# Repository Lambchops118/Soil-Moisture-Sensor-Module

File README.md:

# Soil-Moisture-Sensor-Module
Self contained, solar powered, MQTT communicating module to send soil update to BUTLER

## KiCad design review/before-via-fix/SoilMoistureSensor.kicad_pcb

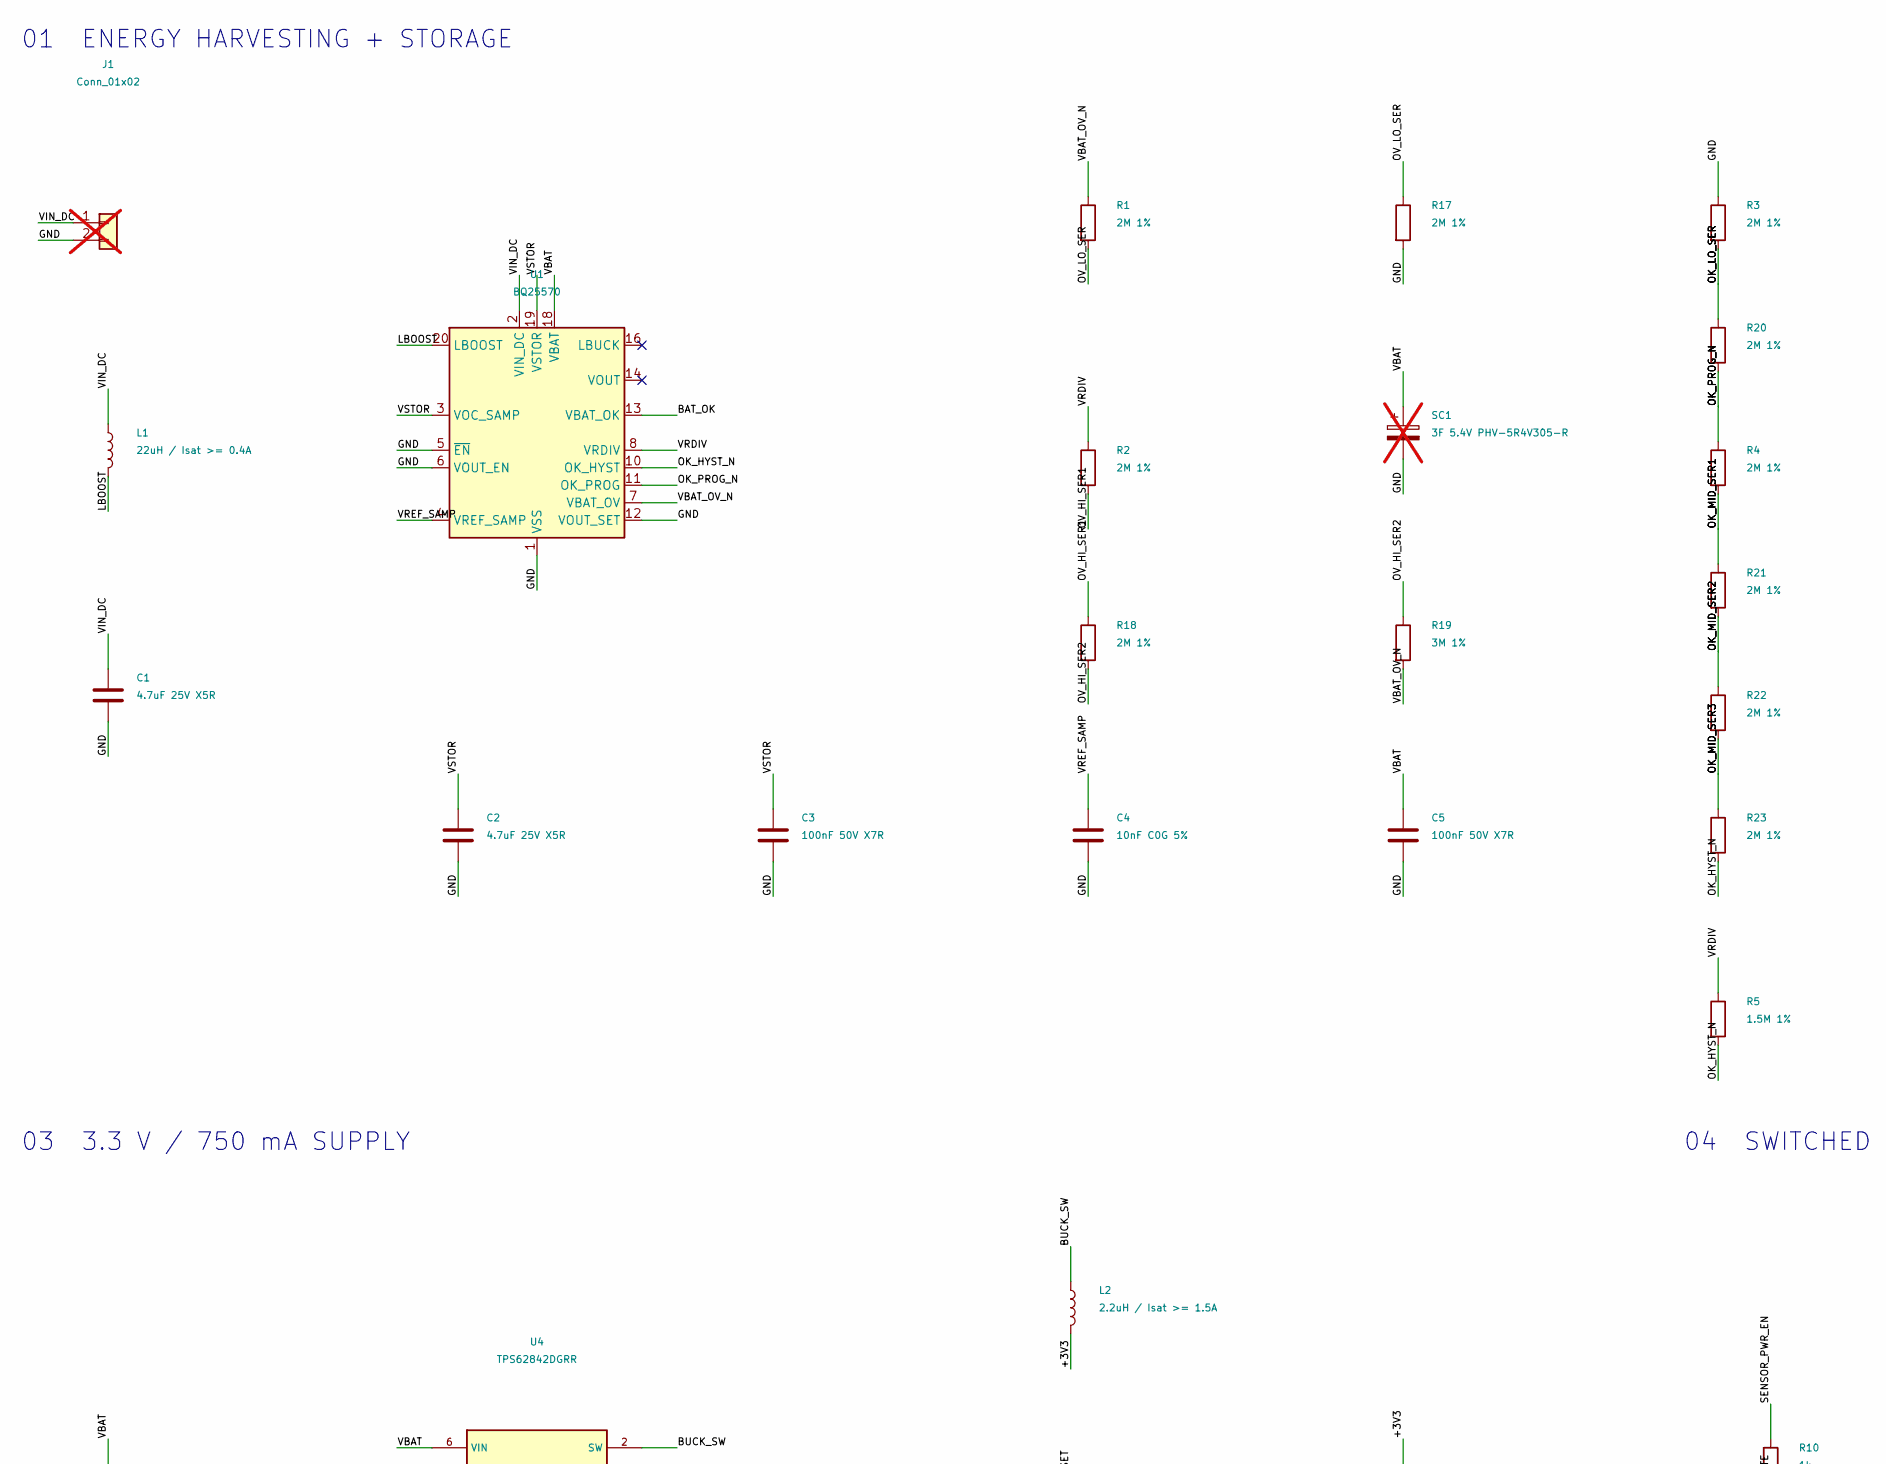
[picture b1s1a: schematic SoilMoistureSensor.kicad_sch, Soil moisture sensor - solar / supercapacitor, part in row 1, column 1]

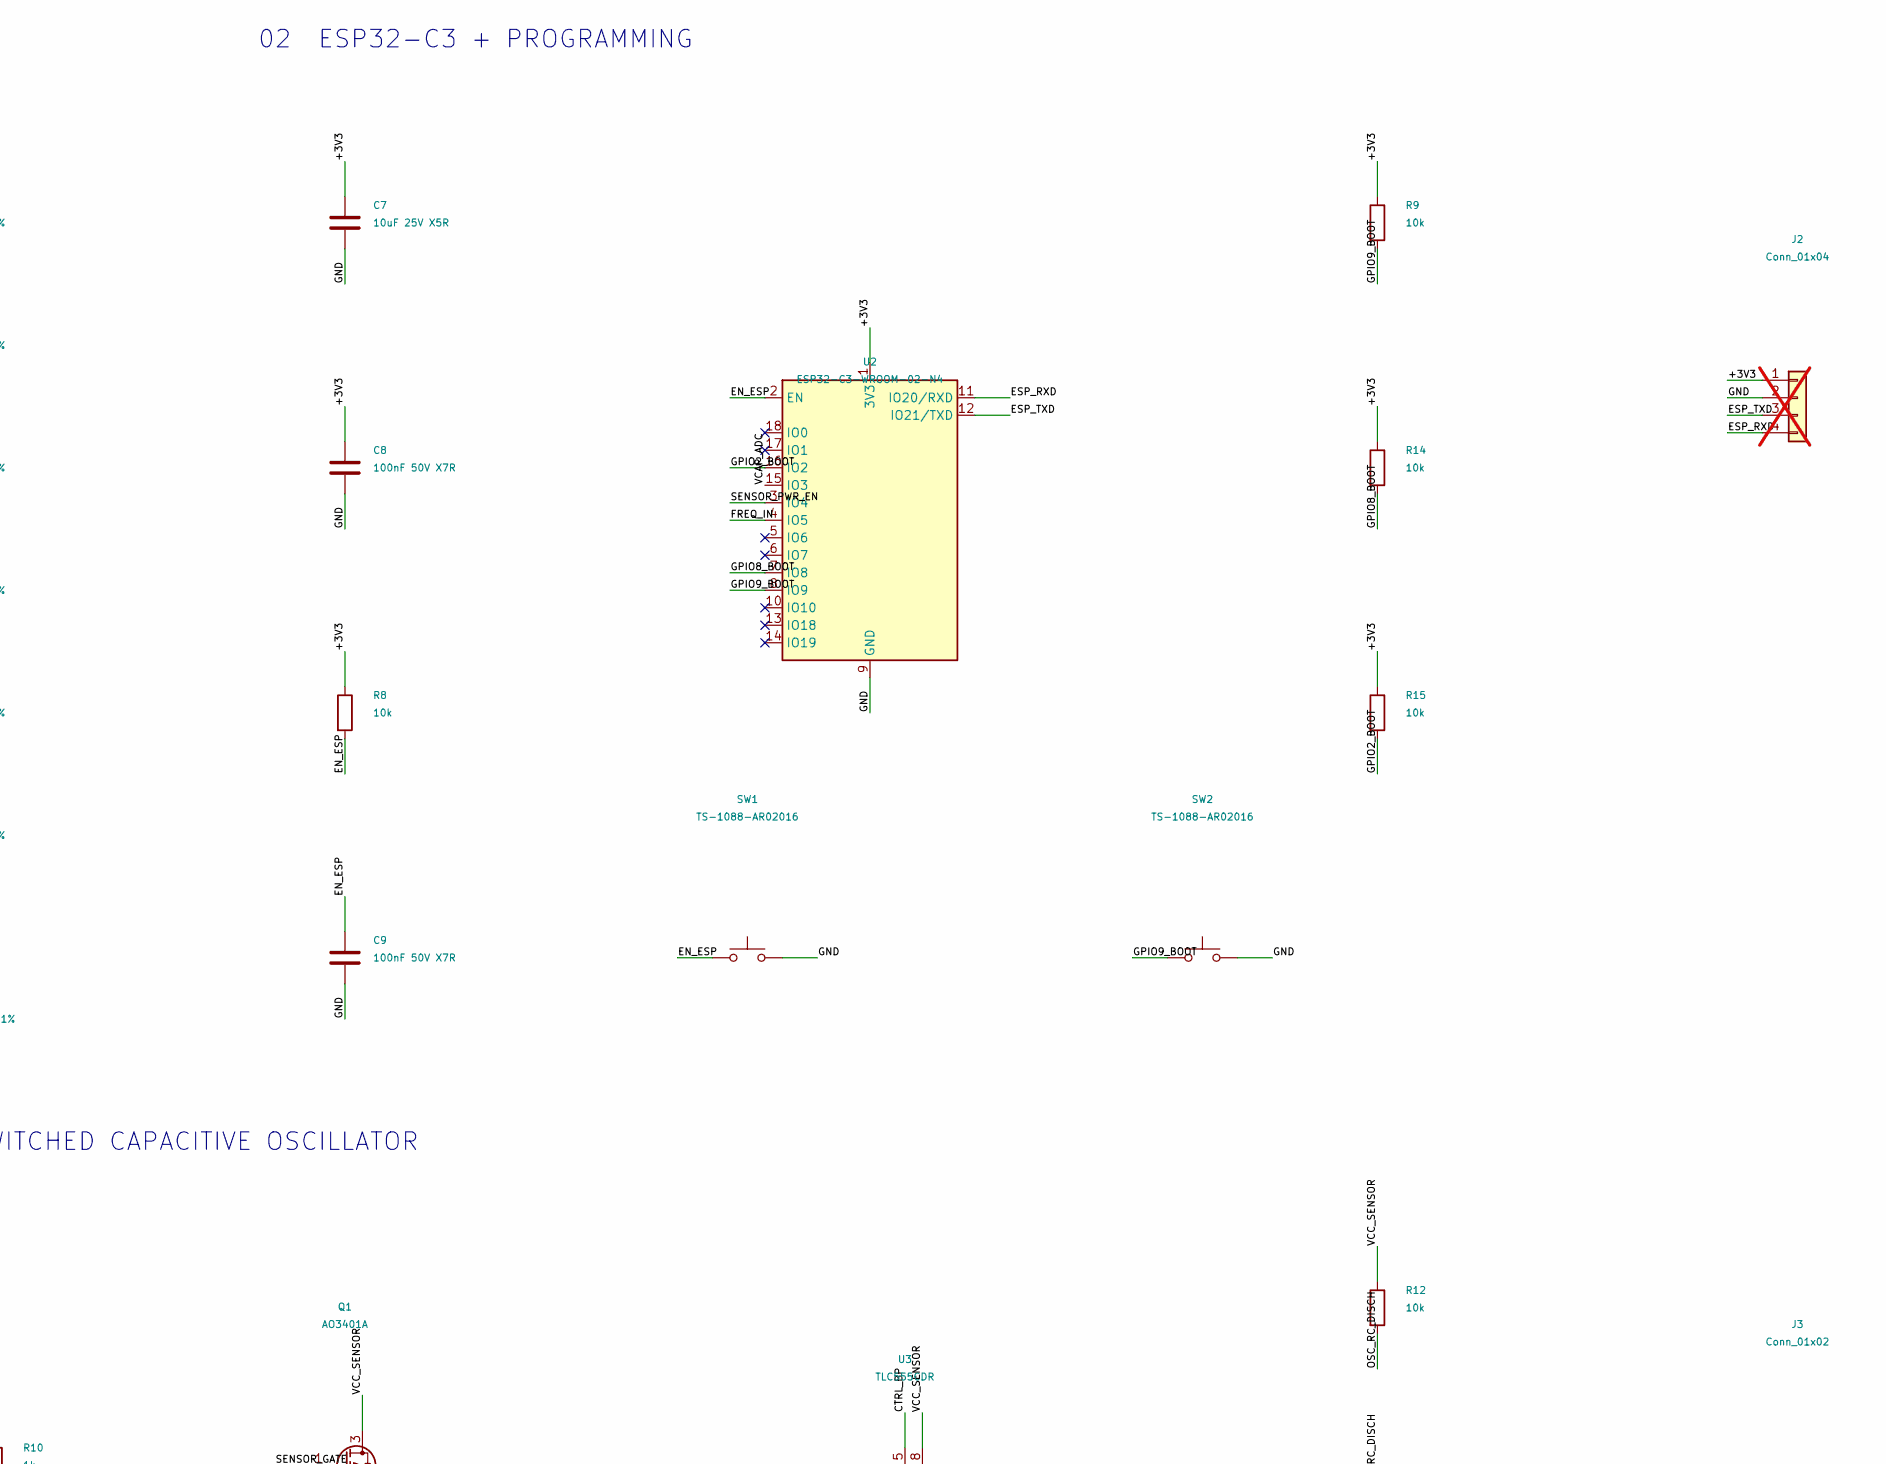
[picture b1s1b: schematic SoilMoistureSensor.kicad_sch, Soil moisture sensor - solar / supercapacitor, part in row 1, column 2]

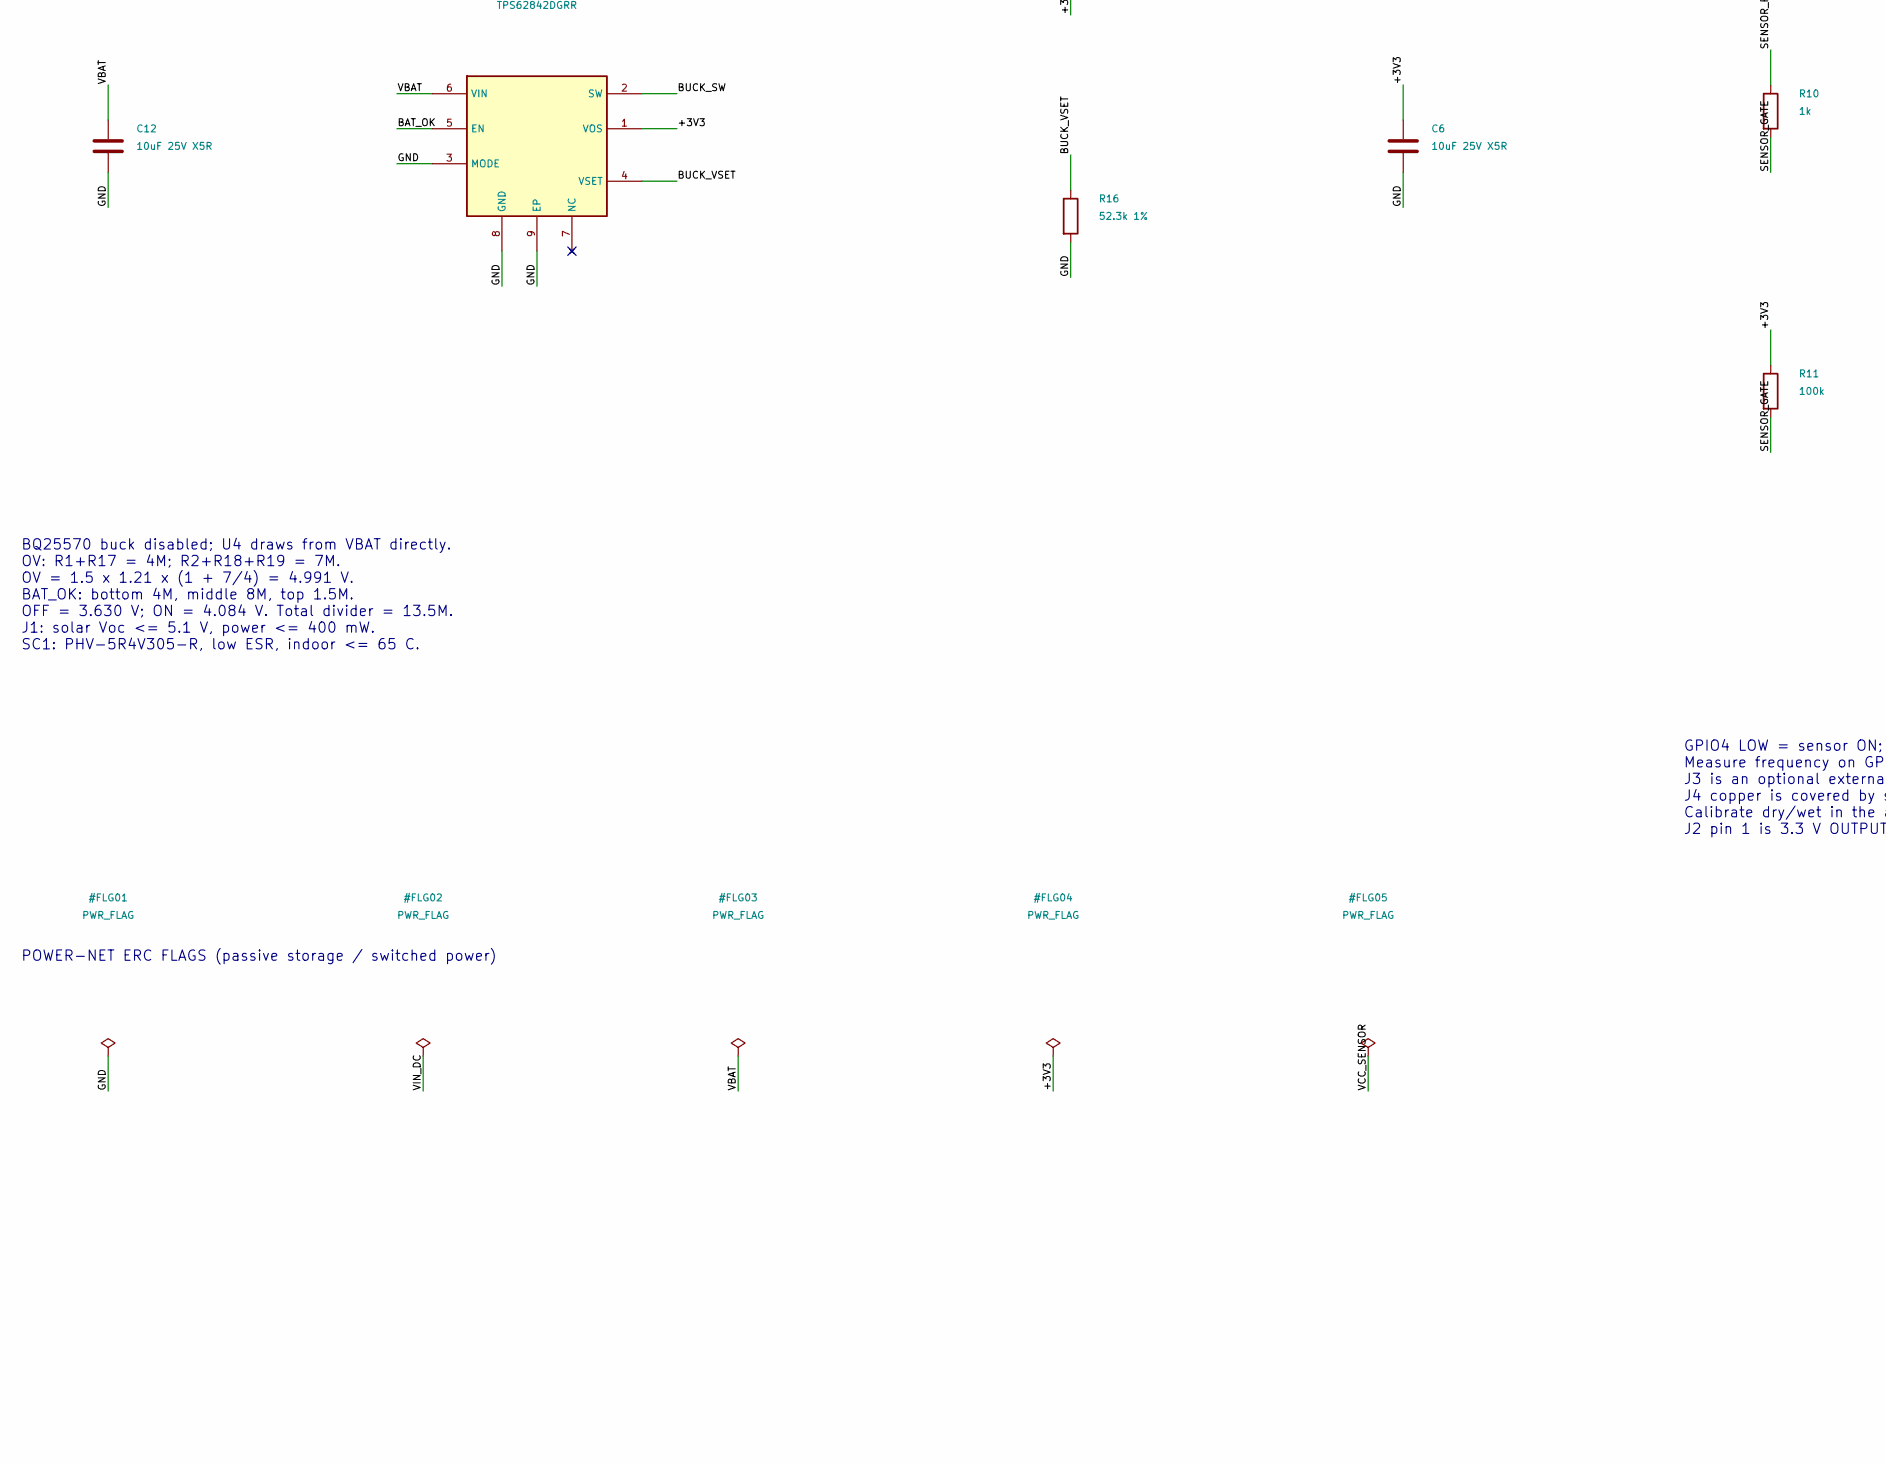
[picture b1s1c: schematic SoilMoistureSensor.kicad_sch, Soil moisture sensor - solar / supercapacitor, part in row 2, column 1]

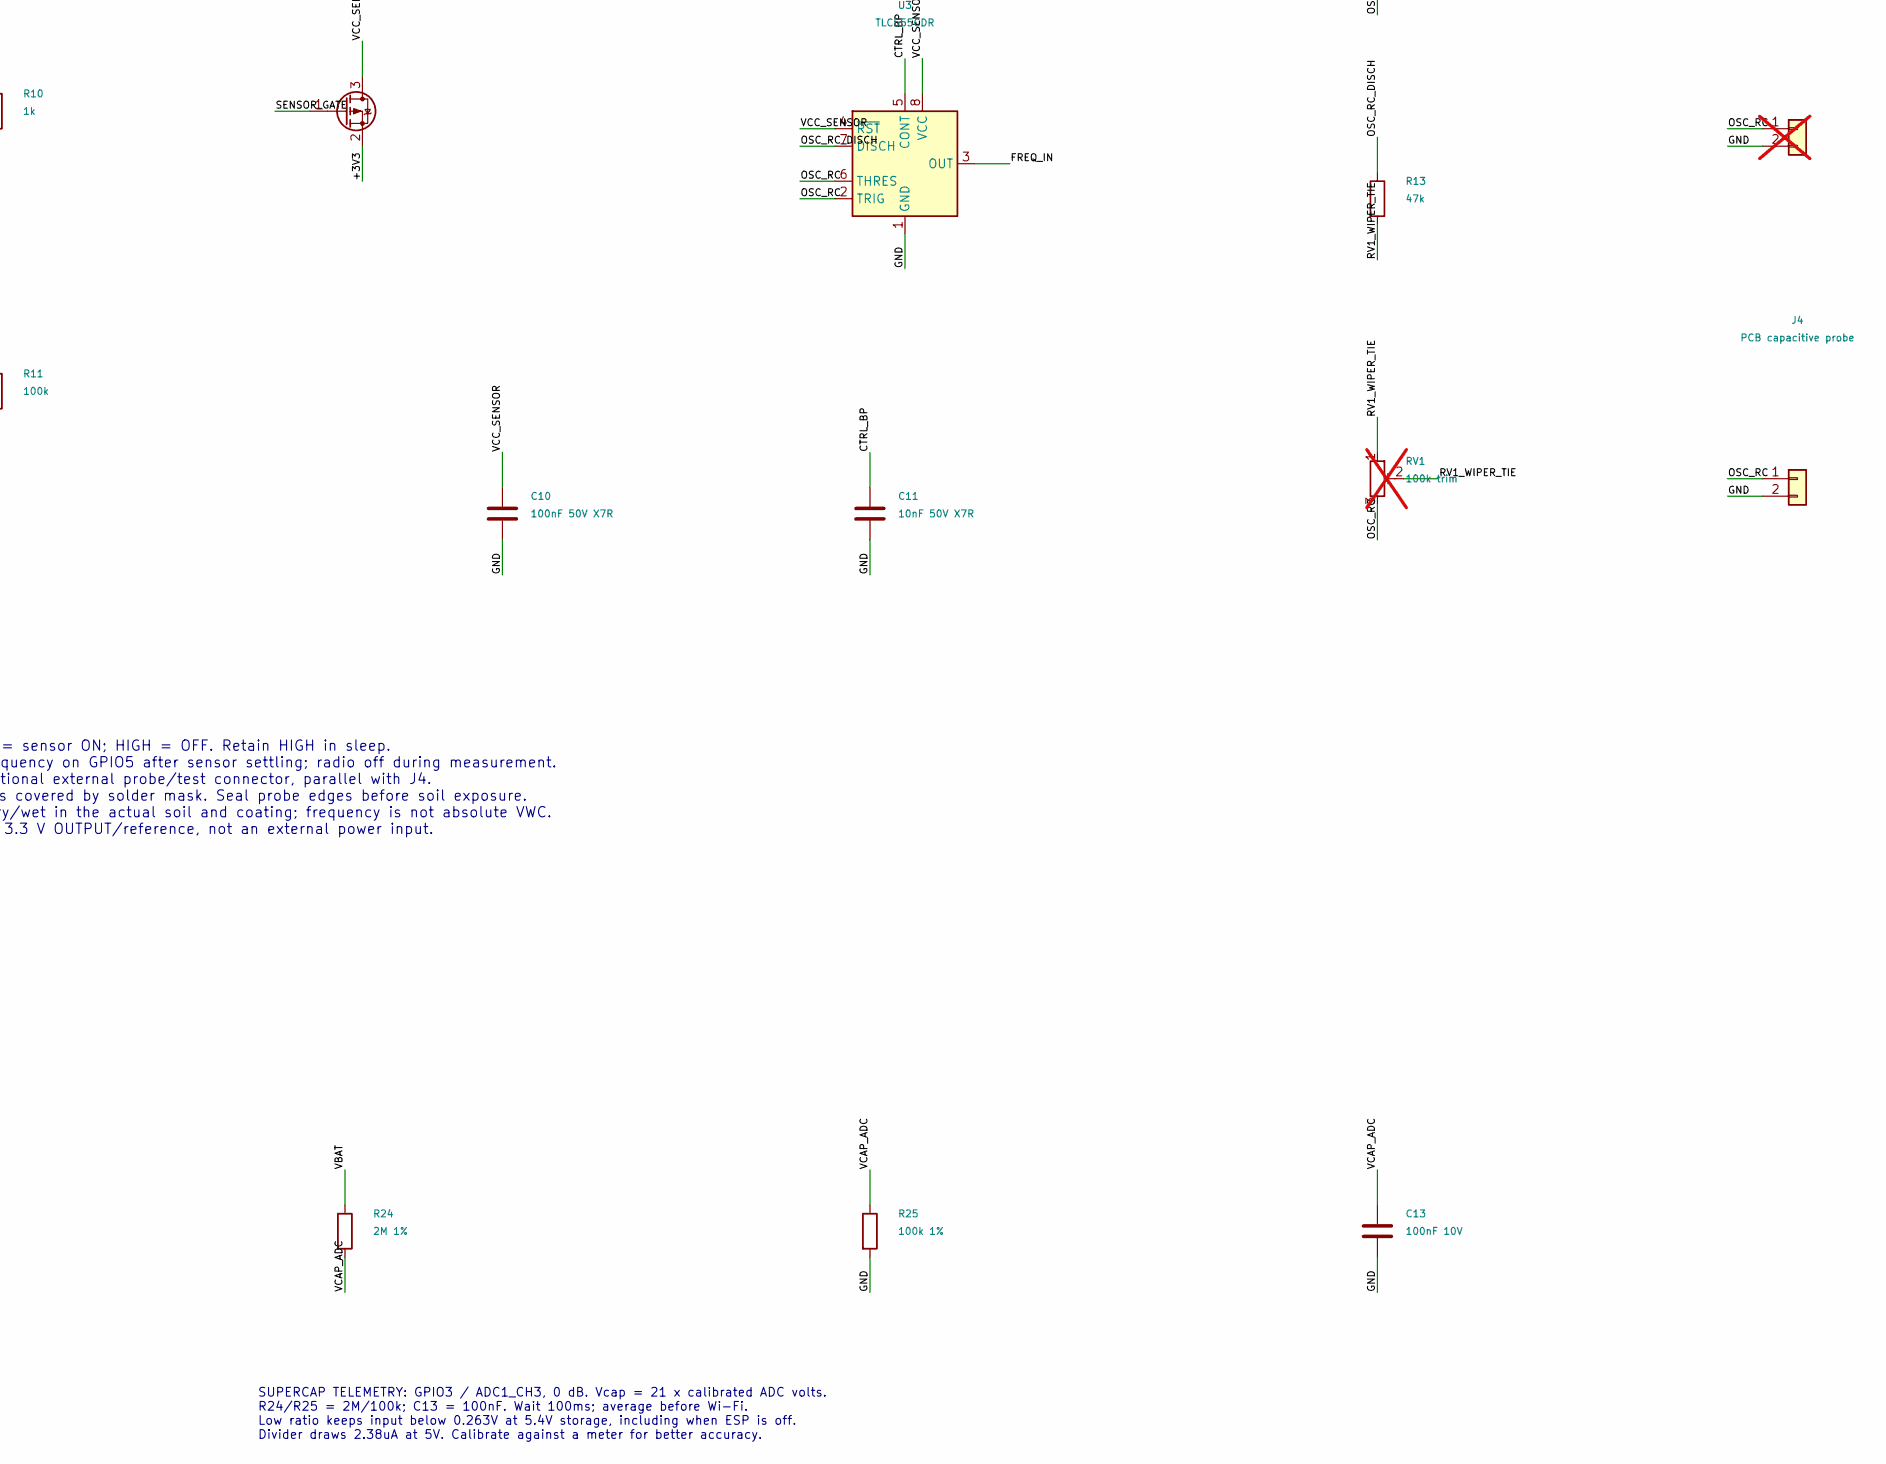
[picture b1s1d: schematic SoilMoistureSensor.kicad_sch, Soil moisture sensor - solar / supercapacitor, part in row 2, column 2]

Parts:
C1, C2: 4.7uF 25V X5R; C_0805_2012Metric; MPN CL21A475KAQNNNE; LCSC C1779
C3, C5, C8, C9, C10: 100nF 50V X7R; C_0805_2012Metric; MPN CC0805KRX7R9BB104; LCSC C49678
C4: 10nF C0G 5%; C_0805_2012Metric; MPN GRM2195C1H103JA01D; LCSC C97905
C6, C7, C12: 10uF 25V X5R; C_0805_2012Metric; MPN CL21A106KAYNNNE; LCSC C15850
C11: 10nF 50V X7R; C_0805_2012Metric; MPN CL21B103KBANNNC; LCSC C1710
C13: 100nF 10V; C_0603_1608Metric; MPN CC0603KRX7R9BB104; LCSC C14663
J1, J3: Conn_01x02; JST_PH_B2B-PH-K_1x02_P2.00mm_Vertical; MPN B2B-PH-K-S(LF)(SN); LCSC C131337; not fitted
J2: Conn_01x04; PinHeader_1x04_P2.54mm_Vertical; MPN B-2100S04P-A110; LCSC C124378; not fitted
J4: PCB capacitive probe; SoilProbe_IDC_40x85mm
L1: 22uH / Isat >= 0.4A; L_Changjiang_FNR4018S; MPN FNR4030S220MT; LCSC C167883
L2: 2.2uH / Isat >= 1.5A; L_Changjiang_FNR4018S; MPN FNR4018S2R2MT; LCSC C167804
Q1: AO3401A; SOT-23; MPN AO3401A; LCSC C15127
R1, R2, R3, R4, R17, R18, R20, R21, R22, R23, R24: 2M 1%; R_0603_1608Metric; MPN 0603WAF2004T5E; LCSC C22976
R5: 1.5M 1%; R_0603_1608Metric; MPN 0603WAF1504T5E; LCSC C4172
R8, R9, R12, R14, R15: 10k; R_0805_2012Metric; MPN 0805W8F1002T5E; LCSC C17414
R10: 1k; R_0805_2012Metric; MPN 0805W8F1001T5E; LCSC C17513
R11: 100k; R_0805_2012Metric; MPN 0805W8F1003T5E; LCSC C149504
R13: 47k; R_0805_2012Metric; MPN 0805W8F4702T5E; LCSC C17713
R16: 52.3k 1%; R_0805_2012Metric; MPN 0805W8F5232T5E; LCSC C17740
R19: 3M 1%; R_0603_1608Metric; MPN 0603WAF3004T5E; LCSC C23156
R25: 100k 1%; R_0603_1608Metric; MPN 0603WAF1003T5E; LCSC C25803
RV1: 100k trim; Potentiometer_Bourns_3296W_Vertical; MPN 3296W-1-104LF; LCSC C48084; not fitted
SC1: 3F 5.4V PHV-5R4V305-R; CP_Eaton_PHV_3F_Vertical_P11.8mm; MPN PHV-5R4V305-R; not fitted
SW1, SW2: TS-1088-AR02016; SW_SPST_TS-1088-xR020; MPN TS-1088-AR02016; LCSC C720477
U1: BQ25570; QFN-20-1EP_3.5x3.5mm_P0.5mm_EP2x2mm; MPN BQ25570RGRR; LCSC C506250
U2: ESP32-C3-WROOM-02-N4; ESP32-C3-WROOM-02_0.3mm_thermal_vias; MPN ESP32-C3-WROOM-02-N4; LCSC C2934560
U3: TLC555CDR; SOIC-8_3.9x4.9mm_P1.27mm; MPN TLC555CDR; LCSC C6986
U4: TPS62842DGRR; HVSSOP-8-1EP_3x3mm_P0.65mm_EP1.57x1.89mm; MPN TPS62842DGRR; LCSC C2873354

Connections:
/+3V3: C6.1, C7.1, C8.1, J2.1, L2.2, Q1.2 (S), R8.1, R9.1, R11.1, R14.1, R15.1, U2.1 (3V3), U4.1 (VOS)
/BAT_OK: U1.13 (VBAT_OK), U4.5 (EN)
/BUCK_SW: L2.1, U4.2 (SW)
/BUCK_VSET: R16.1, U4.4 (VSET)
/CTRL_BP: C11.1, U3.5 (CONT)
/EN_ESP: C9.1, R8.2, SW1.1, U2.2 (EN)
/ESP_RXD: J2.4, U2.11 (IO20/RXD)
/ESP_TXD: J2.3, U2.12 (IO21/TXD)
/FREQ_IN: U2.4 (IO5), U3.3 (OUT)
/GND: C1.2, C2.2, C3.2, C4.2, C5.2, C6.2, C7.2, C8.2, C9.2, C10.2, C11.2, C12.2, C13.2, J1.2, J2.2, J3.2, J4.2, R3.1, R16.2, R17.2, R25.2, SC1.2, SW1.2, SW2.2, U1.1 (VSS), U1.5 (~EN), U1.6 (VOUT_EN), U1.9 (VSS), U1.12 (VOUT_SET), U1.15 (VSS), U1.17 (VSS), U1.21 (VSS), U2.9 (GND), U2.19 (GND), U3.1 (GND), U4.3 (MODE), U4.8 (GND), U4.9 (EP)
/GPIO2_BOOT: R15.2, U2.16 (IO2)
/GPIO8_BOOT: R14.2, U2.7 (IO8)
/GPIO9_BOOT: R9.2, SW2.1, U2.8 (IO9)
/LBOOST: L1.2, U1.20 (LBOOST)
/OK_HYST_N: R5.2, R23.2, U1.10 (OK_HYST)
/OK_LO_SER: R3.2, R20.1
/OK_MID_SER1: R4.2, R21.1
/OK_MID_SER2: R21.2, R22.1
/OK_MID_SER3: R22.2, R23.1
/OK_PROG_N: R4.1, R20.2, U1.11 (OK_PROG)
/OSC_RC: J3.1, J4.1, RV1.3, U3.2 (TRIG), U3.6 (THRES)
/OSC_RC_DISCH: R12.2, R13.1, U3.7 (DISCH)
/OV_HI_SER1: R2.2, R18.1
/OV_HI_SER2: R18.2, R19.1
/OV_LO_SER: R1.2, R17.1
/RV1_WIPER_TIE: R13.2, RV1.1, RV1.2
/SENSOR_GATE: Q1.1 (G), R10.2, R11.2
/SENSOR_PWR_EN: R10.1, U2.3 (IO4)
/VBAT: C5.1, C12.1, R24.1, SC1.1, U1.18 (VBAT), U4.6 (VIN)
/VBAT_OV_N: R1.1, R19.2, U1.7 (VBAT_OV)
/VCAP_ADC: C13.1, R24.2, R25.1, U2.15 (IO3)
/VCC_SENSOR: C10.1, Q1.3 (D), R12.1, U3.4 (~RST), U3.8 (VCC)
/VIN_DC: C1.1, J1.1, L1.1, U1.2 (VIN_DC)
/VRDIV: R2.1, R5.1, U1.8 (VRDIV)
/VREF_SAMP: C4.1, U1.4 (VREF_SAMP)
/VSTOR: C2.1, C3.1, U1.3 (VOC_SAMP), U1.19 (VSTOR)

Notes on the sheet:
01 ENERGY HARVESTING + STORAGE
02 ESP32-C3 + PROGRAMMING
03 3.3 V / 750 mA SUPPLY
04 SWITCHED CAPACITIVE OSCILLATOR
BQ25570 buck disabled; U4 draws from VBAT directly. OV: R1+R17 = 4M; R2+R18+R19 = 7M. OV = 1.5 x 1.21 x (1 + 7/4) = 4.991 V. BAT_OK: bottom 4M, middle 8M, top 1.5M. OFF = 3.630 V; ON = 4.084 V. Total divider = 13.5M. J1: solar Voc <= 5.1 V, power <= 400 mW. SC1: PHV-5R4V305-R, low ESR, indoor <= 65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
GPIO4 LOW = sensor ON; HIGH = OFF. Retain HIGH in sleep. Measure frequency on GPIO5 after sensor settling; radio off during measurement. J3 is an optional external probe/test connector, parallel with J4. J4 copper is covered by solder mask. Seal probe edges before soil exposure. Calibrate dry/wet i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
POWER-NET ERC FLAGS (passive storage / switched power)
SUPERCAP TELEMETRY: GPIO3 / ADC1_CH3, 0 dB. Vcap = 21 x calibrated ADC volts. R24/R25 = 2M/100k; C13 = 100nF. Wait 100ms; average before Wi-Fi. Low ratio keeps input below 0.263V at 5.4V storage, including when ESP is off. Divider draws 2.38uA at 5V. Calibrate against a meter for better accuracy.

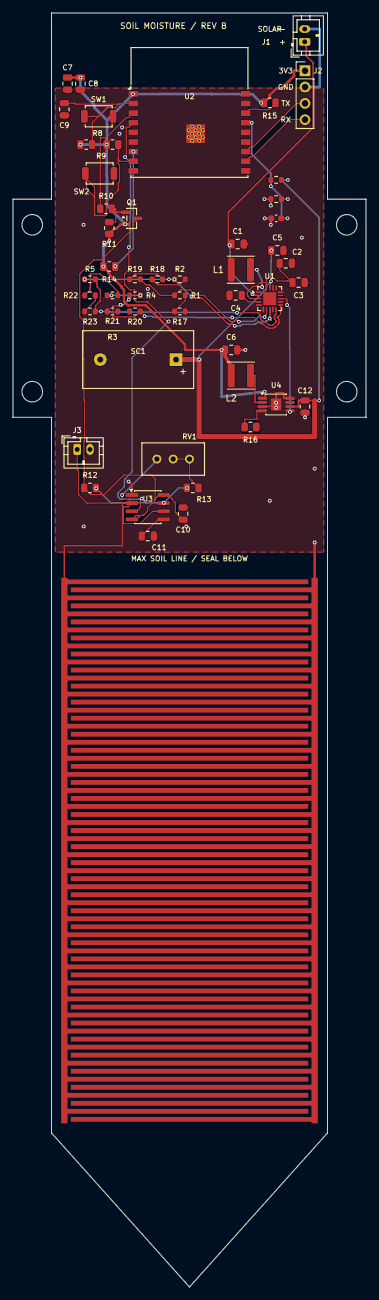
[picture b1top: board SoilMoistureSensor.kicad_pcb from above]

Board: 2 copper layers, 55.0 x 198.5 mm, 55 parts (0 on the bottom side), 36 nets.

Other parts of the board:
H1, H2, H3, H4: Panel carrier M3; MountingHole_3.2mm_M3

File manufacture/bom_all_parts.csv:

Designator,Quantity,Value,Footprint,Manufacturer,MPN,LCSC Part #,Assembly,Source URL,Notes
U1,1,BQ25570,QFN-20-1EP_3.5x3.5mm_P0.5mm_EP2x2mm,Texas Instruments,BQ25570RGRR,C506250,JLCPCB SMT,https://www.lcsc.com/product-detail/C506250.html,Extended; no Basic or Preferred energy-harvesting charger exists at JLCPCB.
U2,1,ESP32-C3-WROOM-02-N4,ESP32-C3-WROOM-02_0.3mm_thermal_vias,Espressif,ESP32-C3-WROOM-02-N4,C2934560,JLCPCB SMT,https://www.lcsc.com/product-detail/C2934560.html,Extended; JLCPCB lists no Basic or Preferred ESP32 module or chip.
U3,1,TLC555CDR,SOIC-8_3.9x4.9mm_P1.27mm,Texas Instruments,TLC555CDR,C6986,JLCPCB SMT,https://www.lcsc.com/product-detail/C6986.html,"Extended. The only Preferred 555 is the bipolar NE555DR, which needs 4.5V and draws mA - unusable on this 3.3V microwatt budget."
U4,1,TPS62842DGRR,HVSSOP-8-1EP_3x3mm_P0.65mm_EP1.57x1.89mm,Texas Instruments,TPS62842DGRR,C2873354,JLCPCB SMT,https://www.lcsc.com/product-detail/C2873354.html,Extended; no Basic or Preferred nanoamp-quiescent buck at JLCPCB.
Q1,1,AO3401A,SOT-23,Alpha & Omega Semiconductor,AO3401A,C15127,JLCPCB SMT,https://www.lcsc.com/product-detail/C15127.html,
L1,1,22uH / Isat >= 0.4A,L_Changjiang_FNR4018S,Changjiang Microelectronics,FNR4030S220MT,C167883,JLCPCB SMT,https://www.lcsc.com/product-detail/C167883.html,"22uH shielded power inductor, 292mOhm, Isat 1.2A, 4x4x3.0mm. Replaces Coilcraft LPS4018-223MRC: 0.53->0.025 USD and lower DCR (was 360mOhm), which matters on the boost side of a microwatt harvester. Still Extended - JLCPCB has no Basic or Preferred power inductor."
L2,1,2.2uH / Isat >= 1.5A,L_Changjiang_FNR4018S,Changjiang Microelectronics,FNR4018S2R2MT,C167804,JLCPCB SMT,https://www.lcsc.com/product-detail/C167804.html,"2.2uH shielded power inductor, 59mOhm, Isat 2.6A, 4x4x1.8mm. Replaces Coilcraft LPS4018-222MRC: 0.98->0.023 USD and lower DCR (was 70mOhm). Shares the FNR40xx land pattern with L1."
"SW1,SW2",2,TS-1088-AR02016,SW_SPST_TS-1088-xR020,XUNPU,TS-1088-AR02016,C720477,JLCPCB SMT,https://www.lcsc.com/product-detail/C720477.html,
"C1,C2",2,4.7uF 25V X5R,C_0805_2012Metric,Samsung Electro-Mechanics,CL21A475KAQNNNE,C1779,JLCPCB SMT,https://www.lcsc.com/product-detail/C1779.html,
"C6,C7,C12",3,10uF 25V X5R,C_0805_2012Metric,Samsung Electro-Mechanics,CL21A106KAYNNNE,C15850,JLCPCB SMT,https://www.lcsc.com/product-detail/C15850.html,
"C3,C5,C8,C9,C10",5,100nF 50V X7R,C_0805_2012Metric,Yageo,CC0805KRX7R9BB104,C49678,JLCPCB SMT,https://www.lcsc.com/product-detail/C49678.html,"Basic: same 0805, 100nF, 50V, X7R, 10% ratings."
C4,1,10nF C0G 5%,C_0805_2012Metric,Murata Electronics,GRM2195C1H103JA01D,C97905,JLCPCB SMT,https://www.lcsc.com/product-detail/C97905.html,10nF 50V C0G 5% 0805. Extended: JLCPCB stocks no Basic or Preferred-extended C0G/NP0 10nF in any package (checked 2026-09-05). Replaces zero-stock C1845387. Do not substitute X7R - this is the MPPT sample-and-hold node.
C11,1,10nF 50V X7R,C_0805_2012Metric,Samsung Electro-Mechanics,CL21B103KBANNNC,C1710,JLCPCB SMT,https://www.lcsc.com/product-detail/C1710.html,
C13,1,100nF 10V,C_0603_1608Metric,Yageo,CC0603KRX7R9BB104,C14663,JLCPCB SMT,https://www.lcsc.com/product-detail/C14663.html,"100nF 50V X7R, exceeds 10V minimum."
"R1,R2,R3,R4,R17,R18,R20,R21,R22,R23,R24",11,2M 1%,R_0603_1608Metric,UNI-ROYAL,0603WAF2004T5E,C22976,JLCPCB SMT,https://www.lcsc.com/product-detail/C22976.html,R24 now 2M; telemetry conversion is 21 times ADC voltage.
R5,1,1.5M 1%,R_0603_1608Metric,UNI-ROYAL,0603WAF1504T5E,C4172,JLCPCB SMT,https://www.lcsc.com/product-detail/C4172.html,1.5M 1%. Preferred-extended tier: no per-part loading fee. In stock 2026-09-05.
R19,1,3M 1%,R_0603_1608Metric,UNI-ROYAL,0603WAF3004T5E,C23156,JLCPCB SMT,https://www.lcsc.com/product-detail/C23156.html,3M 1%. Preferred-extended tier: no per-part loading fee. In stock 2026-09-05.
R25,1,100k 1%,R_0603_1608Metric,UNI-ROYAL,0603WAF1003T5E,C25803,JLCPCB SMT,https://www.lcsc.com/product-detail/C25803.html,
"R8,R9,R12,R14,R15",5,10k,R_0805_2012Metric,UNI-ROYAL,0805W8F1002T5E,C17414,JLCPCB SMT,https://www.lcsc.com/product-detail/C17414.html,
R10,1,1k,R_0805_2012Metric,UNI-ROYAL,0805W8F1001T5E,C17513,JLCPCB SMT,https://www.lcsc.com/product-detail/C17513.html,
R11,1,100k,R_0805_2012Metric,UNI-ROYAL,0805W8F1003T5E,C149504,JLCPCB SMT,https://www.lcsc.com/product-detail/C149504.html,
R13,1,47k,R_0805_2012Metric,UNI-ROYAL,0805W8F4702T5E,C17713,JLCPCB SMT,https://www.lcsc.com/product-detail/C17713.html,
R16,1,52.3k 1%,R_0805_2012Metric,UNI-ROYAL,0805W8F5232T5E,C17740,JLCPCB SMT,https://www.lcsc.com/product-detail/C17740.html,"52.3k 1%. Extended and unavoidable: TPS62842 decodes 3.3V only from RSET 50.21k-54.39k and JLCPCB has no Basic or Preferred 52.3k. The nearest Basic value (51k, C17737) leaves under 0.6% margin to the window edge before tempco."
"J1,J3",2,Conn_01x02,JST_PH_B2B-PH-K_1x02_P2.00mm_Vertical,JST,B2B-PH-K-S(LF)(SN),C131337,Hand solder,https://www.lcsc.com/product-detail/C131337.html,Retain original manual-assembly policy; J3 optional. Mate with PHR-2 housing and SPH-002T-P0.5S contacts. JST specifies PCB thickness 0.8-1.6mm.
J2,1,Conn_01x04,PinHeader_1x04_P2.54mm_Vertical,Ckmtw,B-2100S04P-A110,C124378,Hand solder,https://www.lcsc.com/product-detail/C124378.html,"Straight 1x4 male header, 2.54mm pitch, 3mm solder tails; programming header optional."
RV1,1,100k trim,Potentiometer_Bourns_3296W_Vertical,Bourns,3296W-1-104LF,C48084,Hand solder,https://www.lcsc.com/product-detail/C48084.html,
SC1,1,3F 5.4V PHV-5R4V305-R,CP_Eaton_PHV_3F_Vertical_P11.8mm,Eaton,PHV-5R4V305-R,,Hand solder - external purchase,https://www.eaton.com/us/en-us/skuPage.PHV-5R4V305-R.html,User-approved LCSC exception. Mouser 504-PHV-5R4V305-R. Essential: 3F 5.4V low-ESR vertical pack; do not replace with a high-ESR memory-backup capacitor.
SOL1 (external),1,123mW solar module,29x23mm rear solder pads,ANYSOLAR,SM141K04L,C22012449,Hand solder - external carrier,https://item.szlcsc.com/23442921.html,Not on main-board CPL. Hand solder <=5 seconds below 400C; no high-temperature reflow.
